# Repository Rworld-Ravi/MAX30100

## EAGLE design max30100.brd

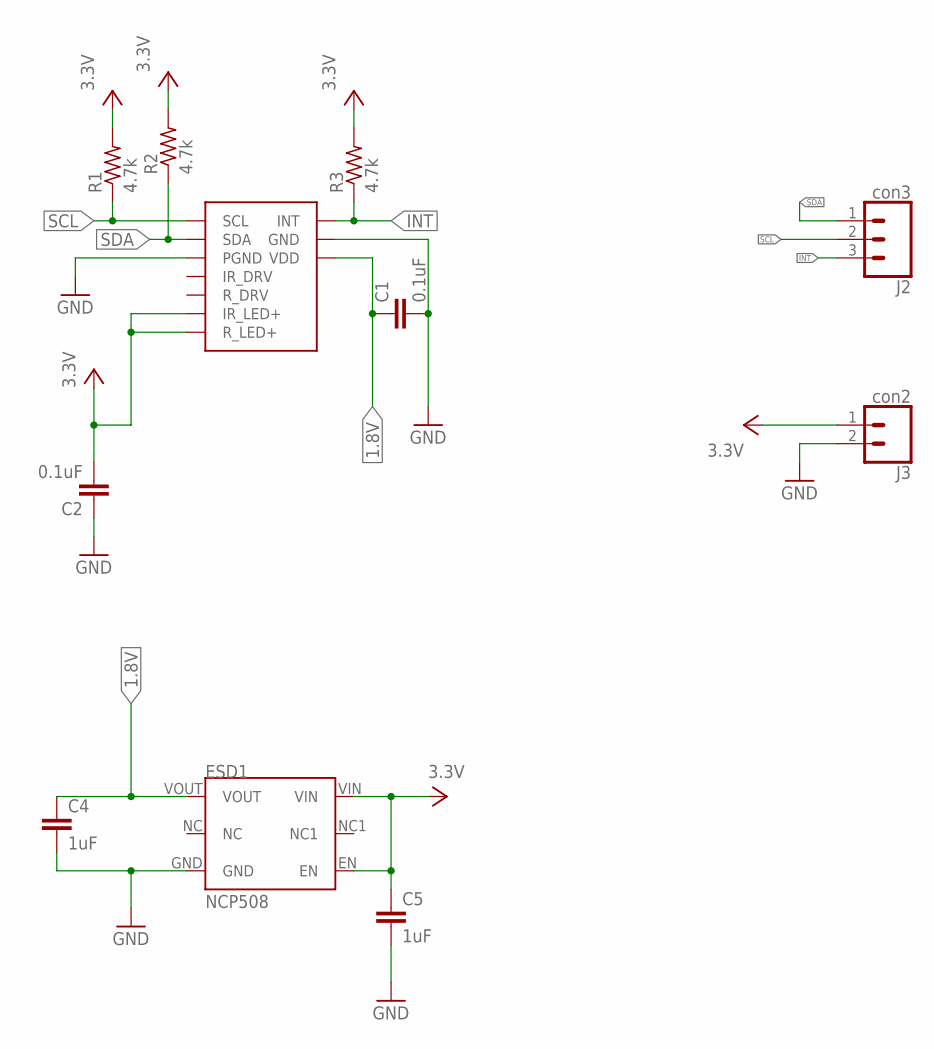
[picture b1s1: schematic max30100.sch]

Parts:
C1, C2: 0.1uF; C0603
C4, C5: 1uF; C0603K
ESD1: NCP508; UQFN6
J2: con3; 1X03
J3: con2; 1X02
R1, R2, R3: 4.7k; R0603
U$1: MAX30100

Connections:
1.8V: C1.1, C4.1, ESD1.VOUT, U$1.11 (VDD)
GND: C1.2, C2.1, C4.2, C5.2, ESD1.GND, J3.2, U$1.4 (PGND), U$1.12 (GND)
INT: J2.3, R3.1, U$1.13 (INT)
SCL: J2.2, R1.1, U$1.2 (SCL)
SDA: J2.1, R2.1, U$1.3 (SDA)
VCC: C2.2, C5.1, ESD1.EN, ESD1.VIN, J3.1, R1.2, R2.2, R3.2, U$1.9 (R_LED+), U$1.10 (IR_LED+)

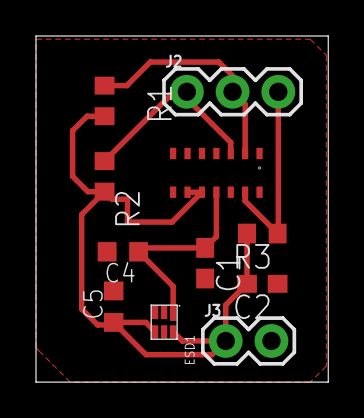
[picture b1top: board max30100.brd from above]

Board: 2 copper layers, 16.2 x 19.2 mm, 11 parts (0 on the bottom side), 6 nets.

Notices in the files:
parts and their libraries:
SparkFun-Connectors: Licensing: Creative Commons ShareAlike 4.0 International - https://creativecommons.org/licenses/by-sa/4.0
